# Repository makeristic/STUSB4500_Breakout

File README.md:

# STUSB4500 USB Power Delivery breakout

A KiCad design for a USB-C Power Delivery sink board built around the STMicroelectronics STUSB4500, with STEMMA QT I²C connectors, screw-terminal power output, and an RGB voltage indicator.

## Status

This is a hobbyist hardware project started in October 2020. The design history includes manufacturing preparation, and fabrication exports are included. The repository description has historically marked the project as work in progress; it does not record electrical validation results or a confirmed production revision.

**Do not use the current source or included Gerbers/drill files for manufacture until the circuit issues are resolved.** A [source audit](docs/code-audit-report.md) found VREG_2V7 tied to the host supply rail and an RGB indicator path from the negotiated supply to a low-voltage controller output. Those circuits require correction and review; the historical exports are not a validated release.

## Features

* Control the STUSB4500 over I²C from a compatible STEMMA QT host, such as an Adafruit board or a SparkFun Qwiic board.
* Configure up to three USB-C PD sink profiles, supported by the [STUSB4500 controller](https://www.st.com/resource/en/datasheet/stusb4500.pdf). This repository does not provide configuration software or a verified board setup procedure.
* Connect downstream devices to the screw terminals.
* Indicate the selected voltage with the RGB LED; the repository does not document a verified colour-to-voltage mapping.
* Four-layer PCB with two STEMMA QT connectors and mounting holes.

## Design files

* [KiCad project](STUSB4500_Breakout.pro), [schematic source](STUSB4500_Breakout.sch), and [PCB layout](STUSB4500_Breakout.kicad_pcb).
* [Schematic PDF](STUSB4500_Breakout.pdf) for viewing without KiCad, and [netlist](STUSB4500_Breakout.net).
* [Gerber and plated/non-plated drill exports](gerber/) for fabrication review.
* [PCB image](images/pcb1.png) and [second 3D view](images/3d2.png).
* [Component and reference-design documents](docs/).
* [Cached historical symbols](STUSB4500_Breakout-cache.lib) and project [symbol](sym-lib-table)/[footprint](fp-lib-table) tables for reproducible library setup.

There is no standalone bill of materials, host firmware, or STUSB4500 configuration tool in this repository. Component values and footprints are recorded in the schematic.

## Open or modify the design

1. Clone this repository, then open `STUSB4500_Breakout.pro` in KiCad. The PCB records KiCad **5.1.7**, and the schematic uses the legacy `.sch` format. Work on a copy when importing into a newer KiCad version.
2. Install the corresponding KiCad standard symbol, footprint, and 3D-model libraries.
3. Clone [Makeristic-KiCad-Library](https://github.com/makeristic/Makeristic-KiCad-Library) alongside this repository. The project tables resolve its legacy symbols and `.pretty` footprints under the nickname `Makeristic-KiCad-Library` from that sibling directory. The design references its MOSFET, mounting-hole, and STEMMA QT logo assets. Keep the committed symbol cache with the schematic; it preserves historical symbol geometry and pin mapping.
4. Resolve missing-library warnings before editing, then review the schematic, PCB, design rules, and fabrication outputs together. Included exports are historical snapshots and have not been regenerated as part of this documentation update.

For nightly KiCad netlist checks, follow the [audit's cache-only export procedure](docs/code-audit-report.md). Globally resolving the same legacy USB symbol in nightly 10.99.0 omitted the shield pin from the export; the audit records the exact conditions. This repository retains its original legacy design formats.

## Feedback and related projects

Use [Issues](https://github.com/makeristic/STUSB4500_Breakout/issues) for questions, build reports, or design corrections. Include the commit, KiCad version, and relevant schematic references; for pull requests, explain electrical changes and which exports you regenerated.

See also the [Feather STM32WB55 board](https://github.com/makeristic/Feather_STM32WB55) and the [Makeristic repository collection](https://github.com/orgs/makeristic/repositories).

## Licence

The original work in this repository remains licensed under [Creative Commons Attribution 4.0 International](https://creativecommons.org/licenses/by/4.0/), as specified by the original README. See [LICENSE](LICENSE) for the full licence text. Attribute Michael Cutler / Makeristic and link to this repository when reusing the original design.

Vendor documents in `docs/`, third-party library elements embedded in the design, cached KiCad symbols, and third-party marks remain subject to their respective owners' terms; the project licence does not relicense those materials. KiCad symbols retain [CC BY-SA 4.0 with the KiCad exception](LICENSES/KiCad-Libraries.md); the [audit](docs/code-audit-report.md) records their source version and provenance.

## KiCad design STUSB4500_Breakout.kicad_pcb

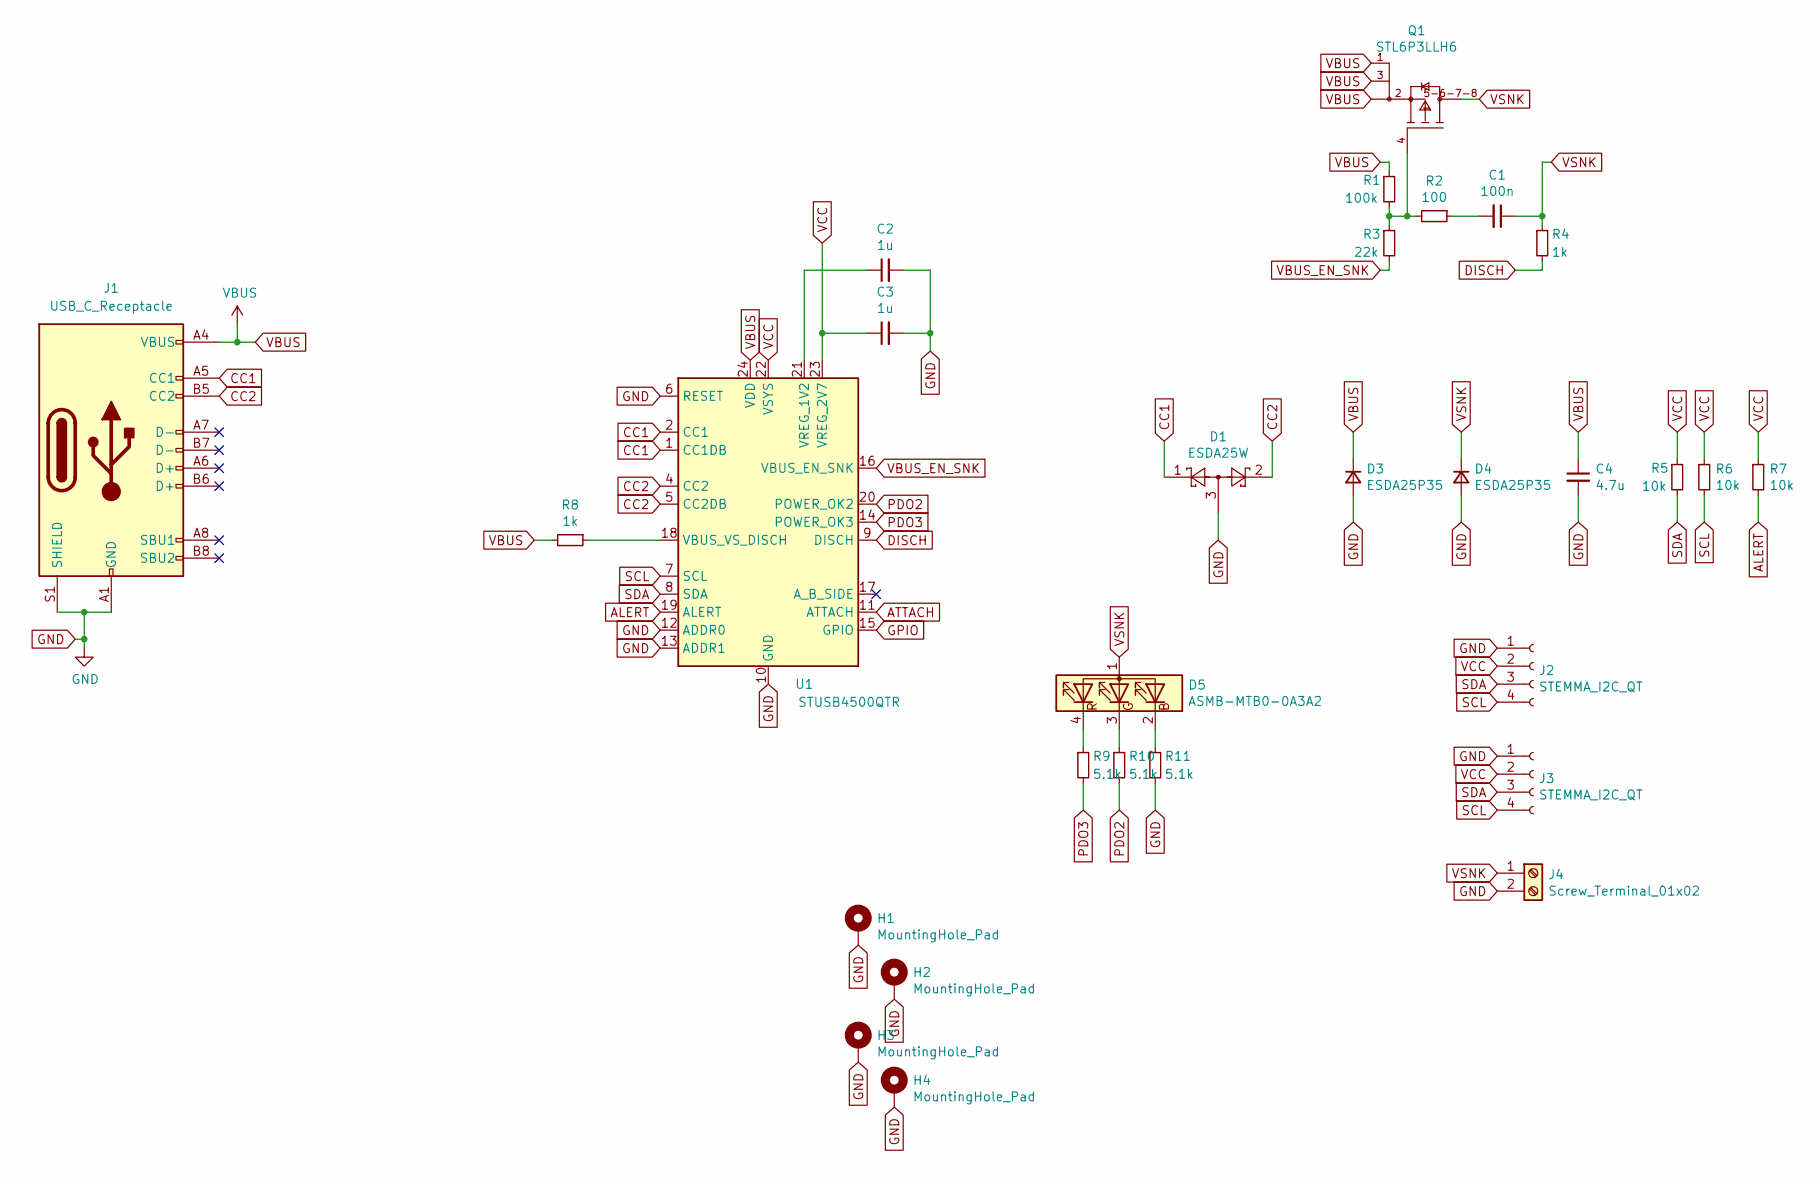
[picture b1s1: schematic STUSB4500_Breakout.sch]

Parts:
C1: 100n; C_0603_1608Metric_Pad1.08x0.95mm_HandSolder
C2, C3: 1u; C_0603_1608Metric_Pad1.08x0.95mm_HandSolder
C4: 4.7u; D_0805_2012Metric_Pad1.15x1.40mm_HandSolder
D1: ESDA25W; SOT-323_SC-70
D3, D4: ESDA25P35; D_0603_1608Metric_Pad1.05x0.95mm_HandSolder
D5: ASMB-MTB0-0A3A2; LED_Avago_PLCC4_3.2x2.8mm_CW
H1, H2, H3, H4: MountingHole_Pad; MountingHole_2.7mm_M2.5_Pad_Small
J1: USB_C_Receptacle; USB_C_Receptacle_XKB_U262-16XN-4BVC11
J2, J3: STEMMA_I2C_QT; JST_SH_SM04B-SRSS-TB_1x04-1MP_P1.00mm_Horizontal
J4: Screw_Terminal_01x02; TerminalBlock_TE_282834-2_1x02_P2.54mm_Horizontal
Q1: STL6P3LLH6; mouser part number 511-STL6P3LLH6; digikey description MOSFET P-CH 30V 6A POWERFLAT
R1: 100k; R_0603_1608Metric_Pad0.98x0.95mm_HandSolder
R2: 100; R_0603_1608Metric_Pad0.98x0.95mm_HandSolder
R3: 22k; R_0603_1608Metric_Pad0.98x0.95mm_HandSolder
R4, R8: 1k; R_0603_1608Metric_Pad0.98x0.95mm_HandSolder
R5, R6, R7: 10k; R_0603_1608Metric_Pad0.98x0.95mm_HandSolder
R9, R10, R11: 5.1k; R_0805_2012Metric_Pad1.20x1.40mm_HandSolder
U1: STUSB4500QTR; QFN-24-1EP_4x4mm_P0.5mm_EP2.7x2.7mm

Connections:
ALERT: R7.2, U1.19 (ALERT); also elsewhere on the board
ATTACH: U1.11 (ATTACH); also elsewhere on the board
CC1: D1.1, J1.A5 (CC1), U1.1 (CC1DB), U1.2 (CC1)
CC2: D1.2, J1.B5 (CC2), U1.4 (CC2), U1.5 (CC2DB)
DISCH: R4.2, U1.9 (DISCH)
GND: C2.2, C3.2, C4.2, D1.3, D3.2 (A), D4.2 (A), H1.1, H2.1, H3.1, H4.1, J1.A1 (GND), J1.A12 (GND), J1.B1 (GND), J1.B12 (GND), J1.S1 (SHIELD), J2.1, J3.1, J4.2, R11.2, U1.6 (RESET), U1.10 (GND), U1.12 (ADDR0), U1.13 (ADDR1), U1.25 (GND)
GPIO: U1.15 (GPIO); also elsewhere on the board
unnamed: C1.2, R2.1
unnamed: C2.1, U1.21 (VREG_1V2)
unnamed: D5.2 (BK), R11.1
unnamed: D5.3 (GK), R10.1
unnamed: D5.4 (RK), R9.1
unnamed: Q1.4 (G), R1.2, R2.2, R3.1
unnamed: R8.1, U1.18 (VBUS_VS_DISCH)
PDO2: R10.2, U1.20 (POWER_OK2)
PDO3: R9.2, U1.14 (POWER_OK3)
SCL: J2.4, J3.4, R6.2, U1.7 (SCL)
SDA: J2.3, J3.3, R5.2, U1.8 (SDA)
VBUS: C4.1, D3.1 (K), J1.A4 (VBUS), J1.A9 (VBUS), J1.B4 (VBUS), J1.B9 (VBUS), Q1.1 (S), Q1.2 (S), Q1.3 (S), R1.1, R8.2, U1.24 (VDD)
VBUS_EN_SNK: R3.2, U1.16 (VBUS_EN_SNK)
VCC: C3.1, J2.2, J3.2, R5.1, R6.1, R7.1, U1.22 (VSYS), U1.23 (VREG_2V7)
VSNK: C1.1, D4.1 (K), D5.1 (A), J4.1, Q1.5-6-7-8 (D), R4.1

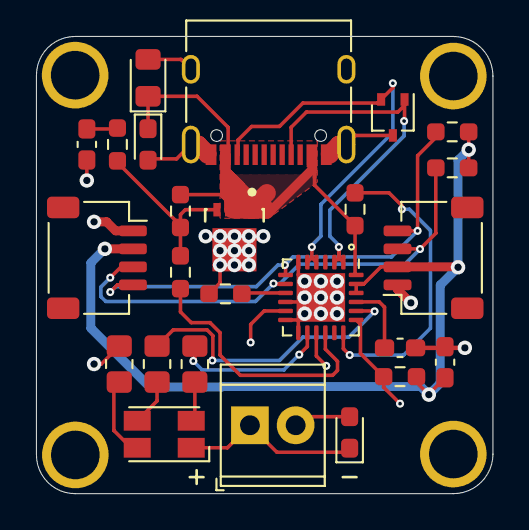
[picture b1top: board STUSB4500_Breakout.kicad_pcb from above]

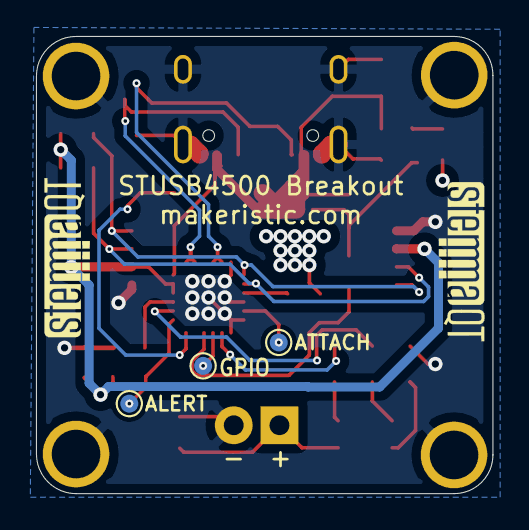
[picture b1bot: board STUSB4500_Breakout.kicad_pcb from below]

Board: 4 copper layers, 25.4 x 25.4 mm, 32 parts (3 on the bottom side), 22 nets.

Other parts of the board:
ALERT: ALERT; TestPoint_Pad_D1.0mm
ATTACH: ATTACH; TestPoint_Pad_D1.0mm
GPIO: GPIO; TestPoint_Pad_D1.0mm

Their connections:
ALERT: ALERT.1; also elsewhere on the board
ATTACH: ATTACH.1; also elsewhere on the board
GPIO: GPIO.1; also elsewhere on the board

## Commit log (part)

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2020-10-20 Updated routing as suggested my Mark Olsson @k0d
2020-10-20 Updated ready for manufacturing

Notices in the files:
README.md:
CC BY 4.0
